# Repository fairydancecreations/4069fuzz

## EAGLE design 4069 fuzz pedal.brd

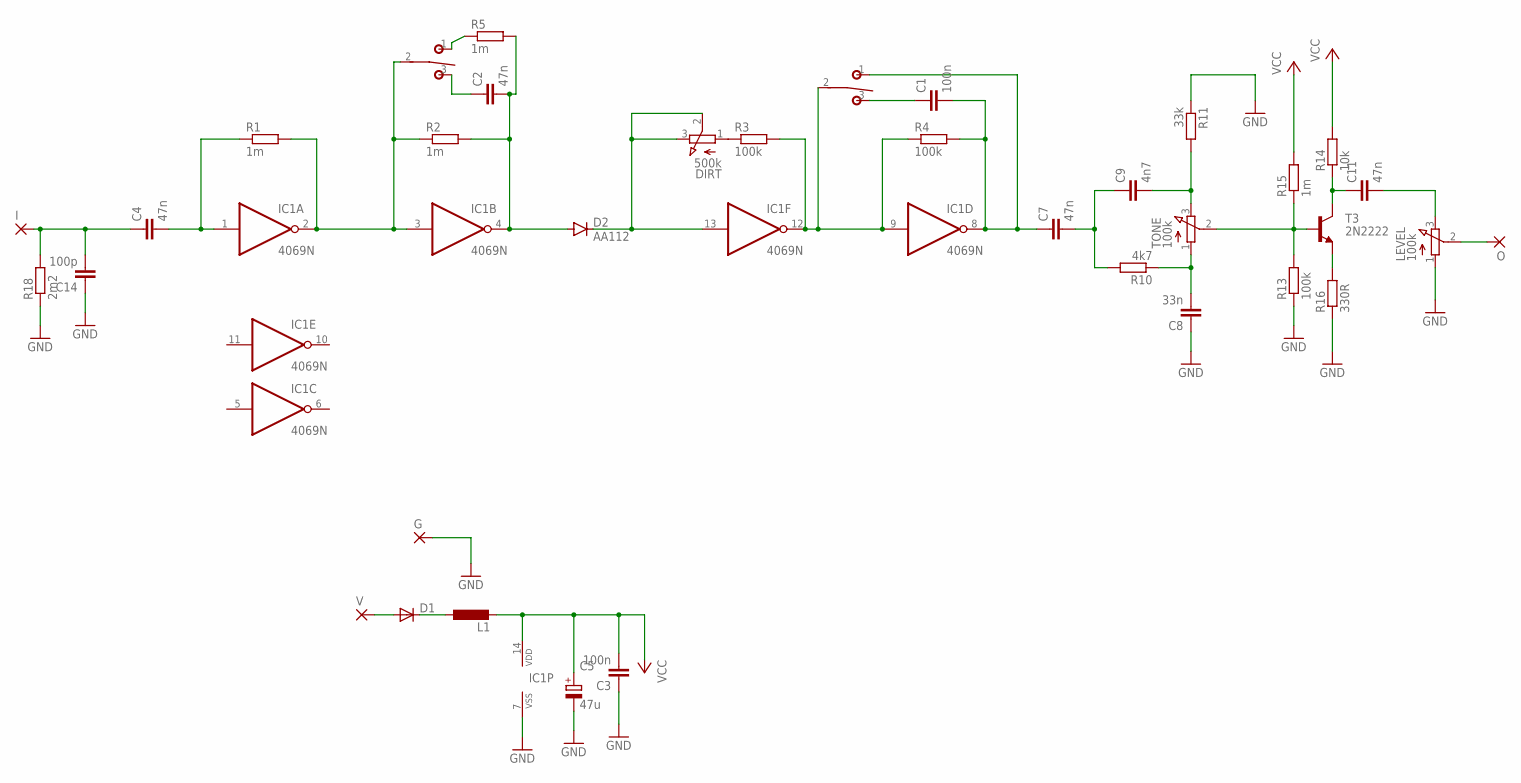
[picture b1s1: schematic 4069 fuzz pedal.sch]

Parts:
C1, C3: 100n; C5B2.5
C2, C4, C7, C11: 47n; C5B2.5
C5: 47u; E2-4
C8: 33n; C5B2.5
C9: 4n7; C5B2.5
C14: 100p; C5B2.5
D1: SMALL_DIODEDO35-7; DO35-7
D2: AA112; DO07
DIRT: 500k; 3RP/1610N
G: 2,15/1,0
I: 2,15/1,0
IC1: 4069N; DIL14
L1: L-EU0204/7; 0204/7
LEVEL: 100k; 3RP/1610N
O: 2,15/1,0
R1, R2, R5, R15: 1m; 0207/7
R3, R4, R13: 100k; 0207/7
R10: 4k7; 0207/7
R11: 33k; 0207/7
R14: 10k; 0207/7
R16: 330R; 0207/7
R18: 2m2; 0207/7
T3: 2N2222; TO18
TONE: 100k; 3RP/1610N
U$1, U$2: T-80-T-SPDT-ON-OFF-ON; M9040P
V: 2,15/1,0

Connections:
GND: C3.1, C5.-, C8.1, C14.1, G.1, IC1.7 (VSS), LEVEL.1 (A), R11.1, R13.1, R16.1, R18.1
unnamed: C2.2, D2.A, IC1.4 (O), R2.2, R5.2
unnamed: IC1.2 (O), IC1.3 (I), R1.2, R2.1, U$2.2
unnamed: DIRT.1 (A), R3.1
unnamed: IC1.9 (I), IC1.12 (O), R3.2, R4.1, U$1.2
unnamed: D2.C, DIRT.2 (S), DIRT.3 (E), IC1.13 (I)
unnamed: C4.2, IC1.1 (I), R1.1
unnamed: C2.1, U$2.3 (S)
unnamed: C4.1, C14.2, I.1, R18.2
unnamed: R5.1, U$2.1 (O)
unnamed: C1.1, U$1.3 (S)
unnamed: D1.C, L1.1
unnamed: D1.A, V.1
unnamed: C9.2, R11.2, TONE.3 (E)
unnamed: C8.2, R10.1, TONE.1 (A)
unnamed: C7.2, C9.1, R10.2
unnamed: R13.2, R15.1, T3.2 (B), TONE.2 (S)
unnamed: C11.1, R14.1, T3.3 (C)
unnamed: R16.2, T3.1 (E)
unnamed: LEVEL.2 (S), O.1
unnamed: C11.2, LEVEL.3 (E)
unnamed: C1.2, C7.1, IC1.8 (O), R4.2, U$1.1 (O)
VCC: C3.2, C5.+, IC1.14 (VDD), L1.2, R14.2, R15.2

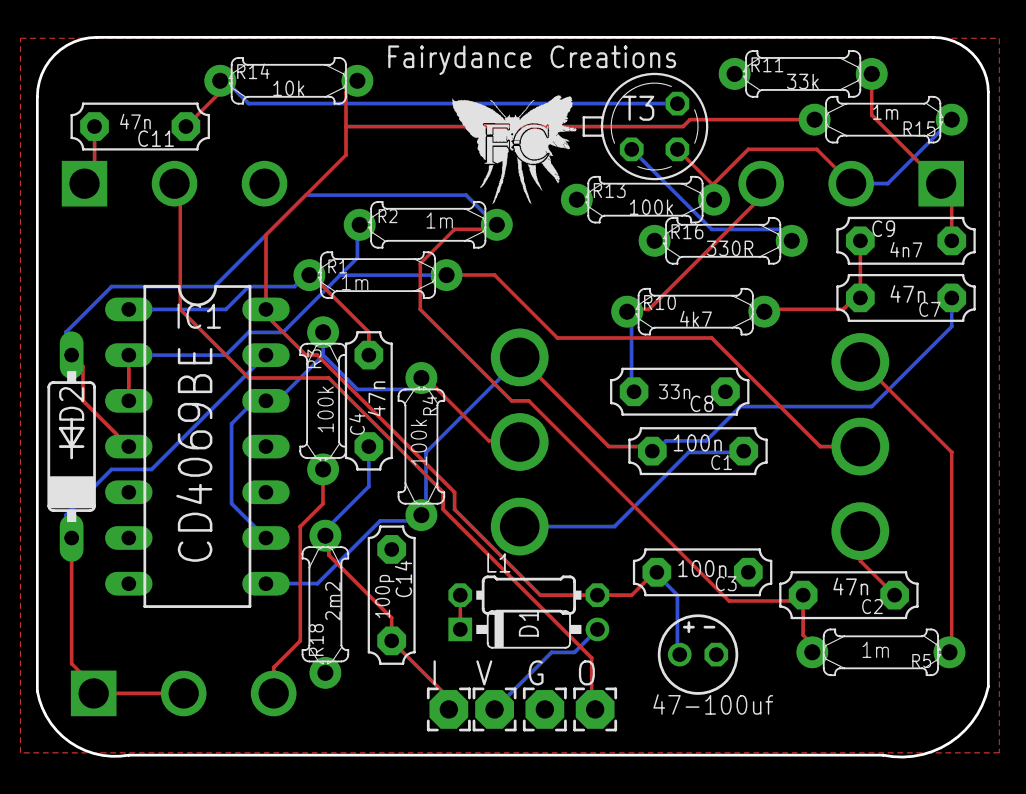
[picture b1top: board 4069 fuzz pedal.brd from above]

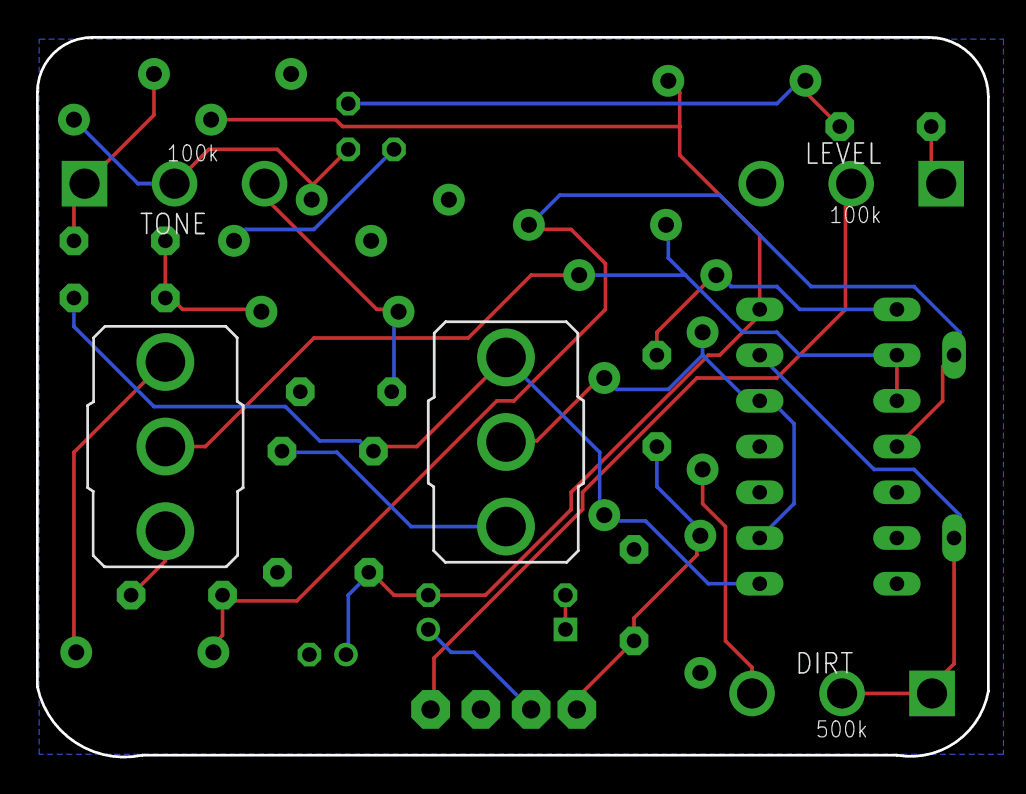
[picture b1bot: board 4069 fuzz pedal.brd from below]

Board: 2 copper layers, 52.8 x 40.0 mm, 36 parts (5 on the bottom side), 23 nets.
